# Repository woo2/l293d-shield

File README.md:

# l293d-shield:
More info to come here.

# Renderings:

### Top

### Bottom

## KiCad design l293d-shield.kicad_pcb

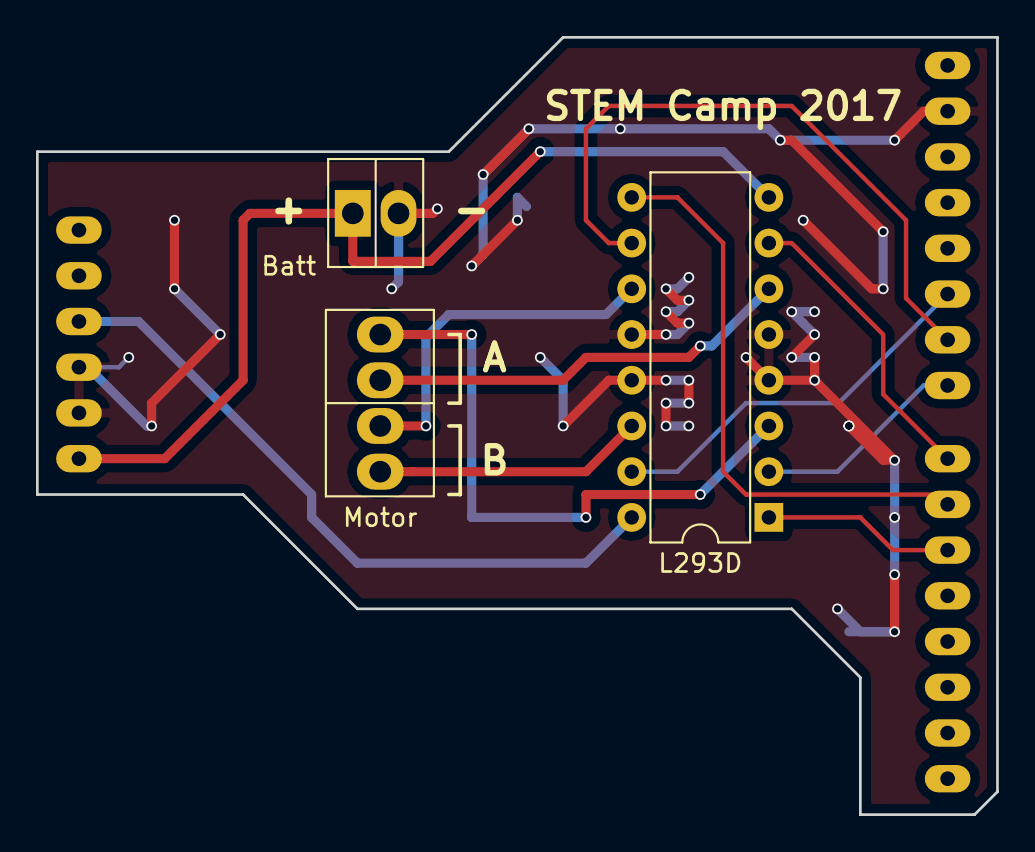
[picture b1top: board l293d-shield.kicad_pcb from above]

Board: 2 copper layers, 53.3 x 43.2 mm, 4 parts (0 on the bottom side), 13 nets.

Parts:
J1: CONN_01X04; Molex_KK-6410-04_04x2.54mm_Straight
J2: CONN_01X02; Molex_KK-6410-02_02x2.54mm_Straight
SHIELD1: ARDUINO_SHIELD; ARDUINO SHIELD
U1: l293d; DIP-16_W7.62mm

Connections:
+5V: SHIELD1.5V, U1.16
/1,2EN: SHIELD1.5, U1.1
/3,4EN: SHIELD1.6, U1.9
/IN1: SHIELD1.8, U1.2
/IN2: SHIELD1.7, U1.7
/IN3: SHIELD1.9, U1.10
/IN4: SHIELD1.10, U1.15
/OUT_1: J1.4, U1.3
/OUT_2: J1.3, U1.6
/OUT_3: J1.2, U1.11
/OUT_4: J1.1, U1.14
GND: J2.2, SHIELD1.GND1, SHIELD1.GND2, SHIELD1.GND3, U1.4, U1.5, U1.12, U1.13
VCC: J2.1, SHIELD1.V_IN, U1.8

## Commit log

2017-06-14 Fix library paths.
2017-06-14 Improve component metadata
2017-06-14 Improve schematic layout
2017-06-28 Add battery connector and footprints
    Add battery connector 1x2 .01" footprint
    Add motor connector 1x4 .01" footprint
    Fix global power nets in schematic
    Add battery connector to shield
2017-06-28 Add readme and renderings
2017-06-29 Improve PCB layout and markings
2017-06-29 Improve power handling
2017-06-29 fix stray trace
2017-06-29 Generaate output files
